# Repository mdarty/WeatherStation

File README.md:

# WeatherStation
ESP32 Weather Station
Weather_Station.jpeg

## WARNING
This is my first C++ program so good luck haha.

## USE
Copy Example_settings.h to settings.h and fill in your info

## Dependincies
All are in the arduino libraries.
  * APRS-IS
  * ArduinoJson
  * driver/adc
  * ESP32Time
  * esp_system
  * LTR390
  * math
  * PubSubClient
  * SparkFunBME280
  * WiFi
  * Wire

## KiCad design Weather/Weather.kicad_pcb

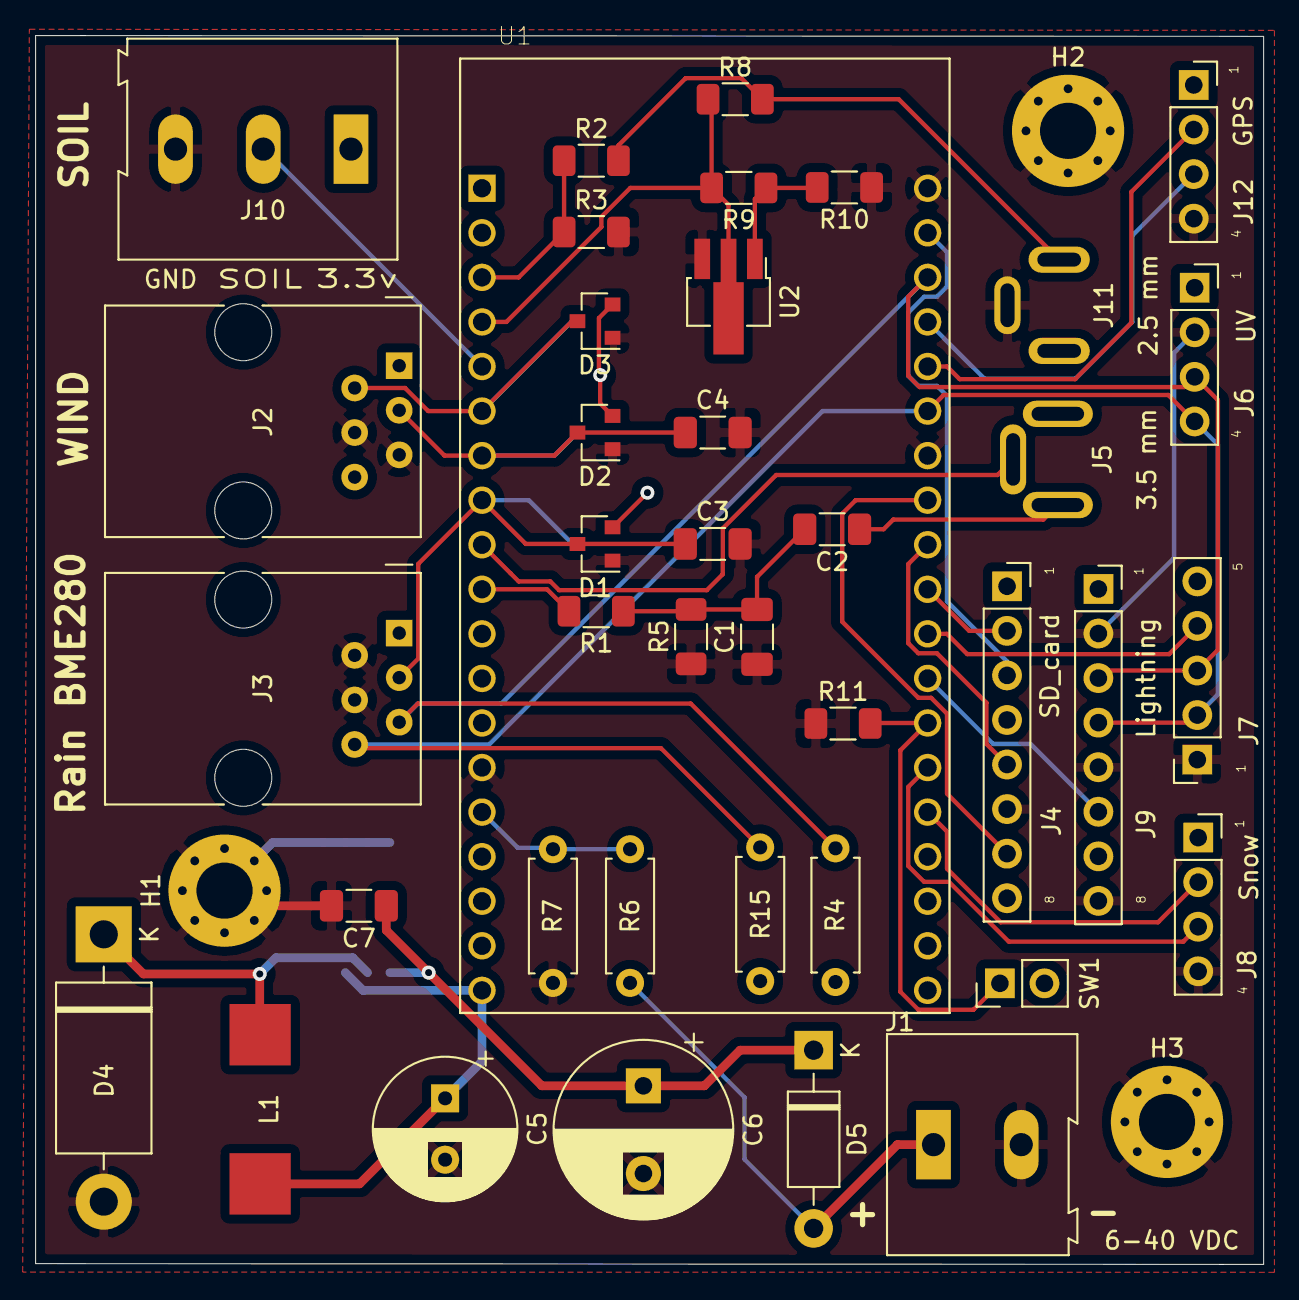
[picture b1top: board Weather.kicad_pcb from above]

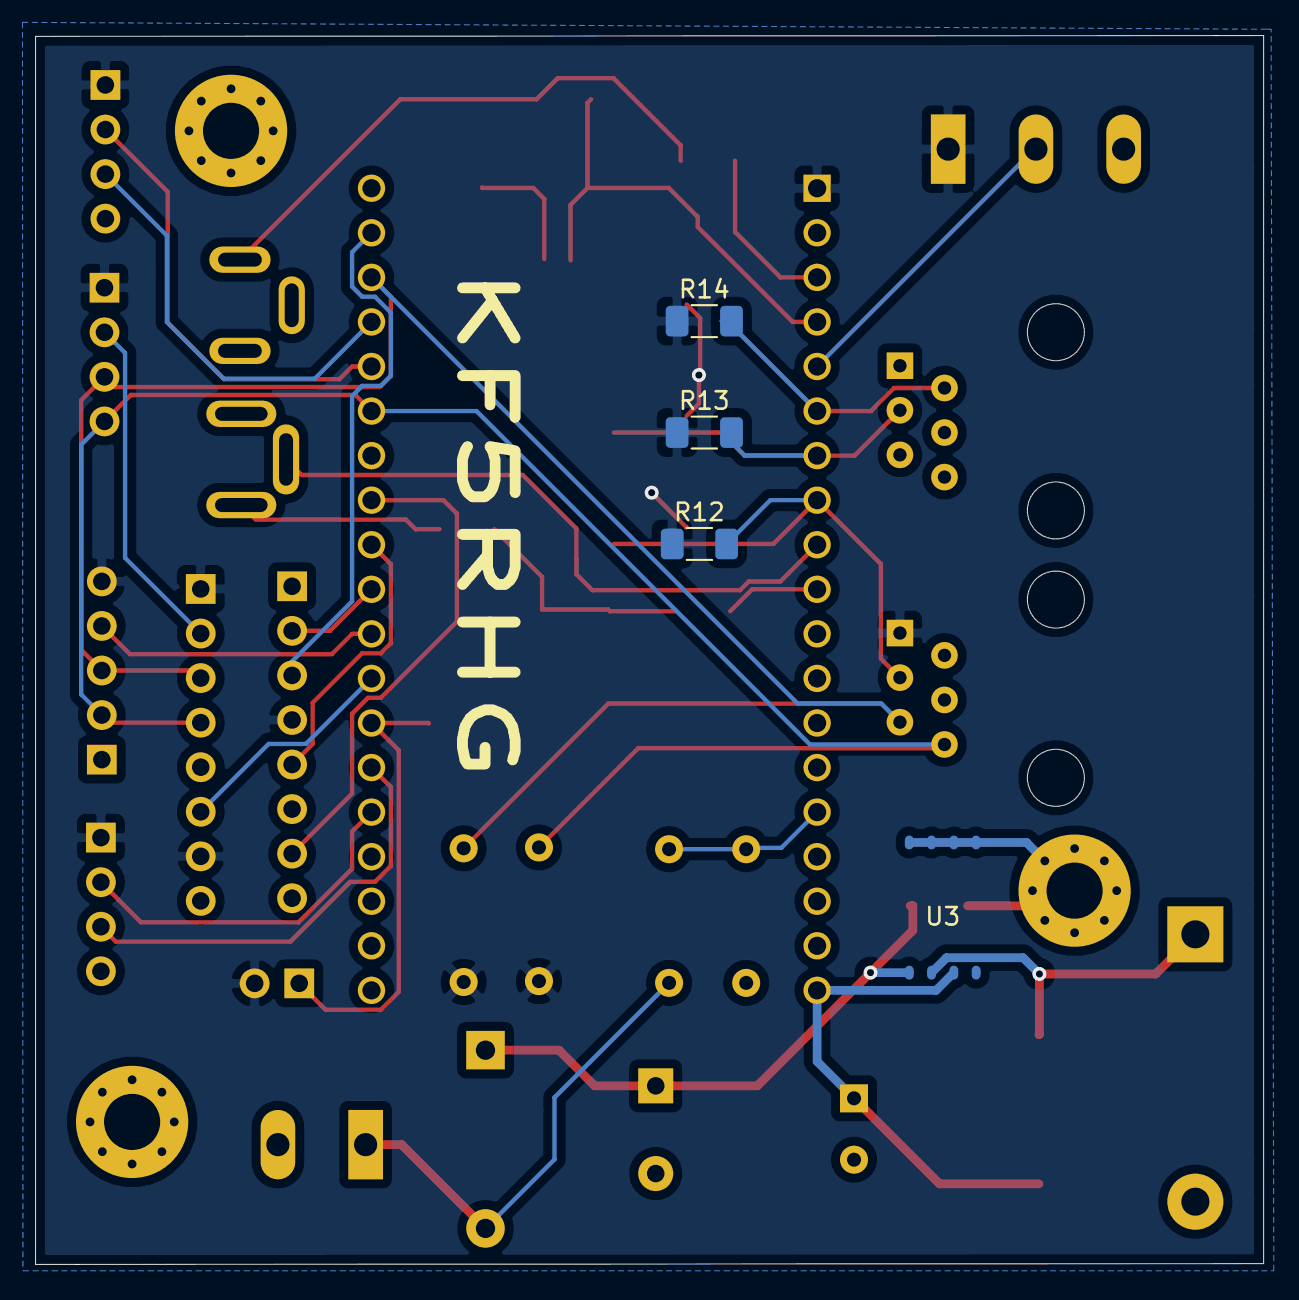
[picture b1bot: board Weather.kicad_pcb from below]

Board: 2 copper layers, 70.0 x 70.0 mm, 47 parts (4 on the bottom side), 32 nets.

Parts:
C1: 4.7nF; C_1206_3216Metric_Pad1.33x1.80mm_HandSolder
C2, C3, C4: 0.1 uF; C_1206_3216Metric_Pad1.33x1.80mm_HandSolder
C5: 180uf/35V; CP_Radial_D8.0mm_P3.50mm
C6: 470uf/35V; CP_Radial_D10.0mm_P5.00mm
C7: 105; C_1206_3216Metric_Pad1.33x1.80mm_HandSolder
D1, D2, D3: BAV99; SOT-23
D4: 1N5820; D_DO-201AD_P15.24mm_Horizontal
D5: 1N5819; D_DO-41_SOD81_P10.16mm_Horizontal
H1, H2: MountingHole_Pad; MountingHole_3.2mm_M3_Pad_Via
H3: MP; MountingHole_3.2mm_M3_Pad_Via
J1: 6-40 VDC; TerminalBlock_Altech_AK300-2_P5.00mm
J2: RJ12 - Wind; RJ12_Amphenol_54601
J3: RJ12 - Rain; RJ12_Amphenol_54601
J4: SD_card; PinSocket_1x08_P2.54mm_Vertical
J5: 3.5 mm; 3.5mm_Stereo_Jack
J6: UV; PinSocket_1x04_P2.54mm_Vertical
J7: RTC; PinSocket_1x05_P2.54mm_Vertical
J8: Snow; PinSocket_1x04_P2.54mm_Vertical
J9: Lightning; PinSocket_1x08_P2.54mm_Vertical
J10: Soil; TerminalBlock_Altech_AK300-3_P5.00mm
J11: 2.5 mm; 2.5mm_Stereo_Jack
J12: GPS; PinSocket_1x04_P2.54mm_Vertical
L1: 68uh/2A; inductor_1004_SMD
R1: 33K; R_1206_3216Metric_Pad1.30x1.75mm_HandSolder
R2, R8: 10K; R_1206_3216Metric_Pad1.30x1.75mm_HandSolder
R3: 3.3K; R_1206_3216Metric_Pad1.30x1.75mm_HandSolder
R4, R6, R7, R15: ??; R_Axial_DIN0207_L6.3mm_D2.5mm_P7.62mm_Horizontal
R5: 1K; R_1206_3216Metric_Pad1.30x1.75mm_HandSolder
R9: 22K; R_1206_3216Metric_Pad1.30x1.75mm_HandSolder
R10: 100K; R_1206_3216Metric_Pad1.30x1.75mm_HandSolder
R11, R14: 10k; R_1206_3216Metric_Pad1.30x1.75mm_HandSolder
R12, R13: 43k; R_1206_3216Metric_Pad1.30x1.75mm_HandSolder
SW1: SW_SPST; PinHeader_1x02_P2.54mm_Vertical
U1: ESP32-DEVKITC-32D; MODULE_ESP32-DEVKITC-32D
U2: CJ431; SOT-89-3_Handsoldering
U3: XL1509-5.0E1; SOIC-8_5x4

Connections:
3.3v: D1.2, D2.2, D3.2, J3.1, J4.4, J6.1, J7.5, J8.1, J9.1, J9.7, J10.1, J12.1, R4.1, R12.1, R13.1, R14.1, R15.1, SW1.2, U1.1
5v: C5.1, L1.1, U1.19, U3.3
ADC: R2.1, R3.1, U1.3
BAT: D5.2, J1.1, R6.1
B_spkr: J11.T, R2.2, R8.2
Chr: R6.2, R7.1, U1.15
DAC: R1.2, U1.10
Echo: J8.3, U1.33
GND: C1.1, C3.2, C4.2, C5.2, C6.2, C7.2, D1.1, D2.1, D3.1, D4.2, H1.1, H2.1, H3.1, J1.2, J2.4, J2.5, J3.2, J3.4, J4.6, J6.2, J7.1, J8.4, J9.2, J9.5, J9.8, J10.3, J11.S, J12.4, R3.2, R5.1, R7.2, R10.1, R11.1, U1.14, U1.20, U1.26, U2.3, U3.5, U3.6, U3.7, U3.8
IRQ: J9.6, U1.31
MFP: J7.4, U1.30
unnamed: C1.2, C2.2, R1.1, R5.2
unnamed: C6.1, C7.1, D5.1, U3.1
unnamed: D4.1, L1.2, U3.2
unnamed: R9.1, R10.2, U2.1
PTT: J5.S, U1.9
RX: J12.2, U1.24
Rain: C3.1, D1.3, J3.3, R12.2, U1.8
SCL: J3.5, J6.3, J7.3, J9.3, R4.2, U1.22
SDA: J3.6, J6.4, J7.2, J9.4, R15.2, U1.25
SD_CS: J4.2, U1.29
SD_safe: R11.2, SW1.1, U1.32
SOIL: J10.2, U1.5
SPI_CIPO: J4.7, U1.27
SPI_COPI: J4.3, U1.21
SPI_SCK: J4.5, U1.28
TX: J12.3, U1.23
Trig: J8.2, U1.34
Wdir: D3.3, J2.2, R14.2, U1.6
Wspd: C4.1, D2.3, J2.3, R13.2, U1.7
b_mic: C2.1, J5.R
trigger: R8.1, R9.2, U1.4, U2.2

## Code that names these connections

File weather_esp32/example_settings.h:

#ifndef SETTINGS_H_
#define SETTINGS_H_

//#define DEBUG
#define APRS
#define MQTT
#define SLEEP

//Debouncing Time in MICROSECONDS (15 Milla seconds)
const int DEBOUNCING_TIME = 15000;

#ifdef DEBUG
  const int report_time = 30000;
#else 
  const int report_time = 300000;
#endif

const int sample_time = 5000;

const char* ntpServer = "SOME NTP SERVER";
const int daylightOffset_sec = 0;
const int gmtOffset_sec = 0;
const unsigned int ntp_time = 3600000;

// Wifi Info
const char* WIFI_NAME = "YOUR WIFI";
const char* WIFI_KEY = "YOUR WIFI PASS";

// Pins
#define I2C_ADDRESS 0x48
const byte RAIN_PIN = 33;
#define WDIR_PIN ADS1115_COMP_0_GND
const byte WSPD_PIN = 32;
//const byte bat_pin = 13;
#define bat_pin ADS1115_COMP_2_GND
#define solar_pin ADS1115_COMP_3_GND
const byte PWM_C = 35;
const byte bat_temp_pin = 27;
const unsigned int solar_full = 2600;
const unsigned int bat_full = 2600; //mV scaled with resistor
const unsigned int bat_emp = 2000; //mV scaled with resistor
#define SOIL_PIN ADS1115_COMP_1_GND
const float Vref = 3291.625;
const unsigned int BULK_CH_SP = 14400;
const unsigned int  FLOAT_CH_SP = 13500;

#ifdef APRS
// Device name and software version
const char *NODENAME = "WxESP";
const char *VERSION = "0.1";
bool       PROBE  = true;                   // True if the station is being probed

const char* APRS_SERVER = "rotate.aprs2.net";
const int   APRS_PORT   = 14580;
const char* APRS_USER   = "YOUR CALLSIGN";
String APRS_SSID   = "-13";
String APRS_HEADER      = ">APRS,TCPIP*:";
const char* APRS_PASS   = "YOUR APRS PIN";
const char* APRS_TOOL   = "ESP32-WX";
const char* APRS_VERS   = "0.1";
String aprsLocation  = "latN/LongW";
#endif

#ifdef MQTT
#include <ArduinoJson.h>
// MQTT
const char* mqtt_server = "MQTT_SERVER";
const int mqtt_port = 1883;
const char* mqtt_clientID = "WeatherStation";
const char* mqtt_user = "MQTT_USER";
const char* mqtt_pass = "MQTT_PASS";
String hassio_topic = "homeassistant/sensor/" + String(mqtt_clientID) + "/";
const int mqtt_buf = 1024;
const char* mqtt_LWT_p = "Online";
String mqtt_LWT = hassio_topic + "LWT";
String mqtt_state_topic = hassio_topic + "state";

String mqtt_configs(byte i) {
  DynamicJsonDocument conf_doc(mqtt_buf);
  JsonObject conf_dev  = conf_doc.createNestedObject("dev");

  conf_dev["name"] = mqtt_clientID;
  conf_dev["mf"] = "Darty";
  conf_dev["sw"] = "0.1";
  conf_dev["ml"] = "Prototype";
  conf_dev["sa"] = "Outside";
  JsonArray ids = conf_dev.createNestedArray("ids");
  ids.add("Prototype");

  switch(i) {
    case 0 :
      conf_doc["unique_id"] = String(mqtt_clientID) + "_temp";
      conf_doc["device_class"] = "temperature";
      conf_doc["name"] = "Outside Temperature";
      conf_doc["unit_of_meas"] = "°F";
      conf_doc["value_template"] = "{{ value_json.Temp }}";
      break;
    case 1 :
      //Humidity
      conf_doc["unique_id"] = String(mqtt_clientID) + "_humidity";
      conf_doc["device_class"] = "humidity";
      conf_doc["name"] = "Outside Humidity";
      conf_doc["unit_of_meas"] = "%";
      conf_doc["value_template"] = "{{ value_json.RH }}";
      break;
    case 2 :
      //Pressure
      conf_doc["unique_id"] = String(mqtt_clientID) + "_pressure";
      conf_doc["device_class"] = "pressure";
      conf_doc["name"] = "Outdoor Temperature";
      conf_doc["unit_of_meas"] = "hPa";
      conf_doc["value_template"] = "{{ value_json.Pres }}";
      break;
    case 3 :
      //Wind Direction
      conf_doc["unique_id"] = String(mqtt_clientID) + "_wind_direction";
      conf_doc["name"] = "Wind Direction";
      conf_doc["icon"] = "mdi:compass";
      conf_doc["unit_of_meas"] = "deg";
      conf_doc["value_template"] = "{{ value_json.wDir }}";
      break;
    case 4 :
      // Wind Speed
      conf_doc["unique_id"] = String(mqtt_clientID) + "_wind_speed";
      conf_doc["name"] = "Wind Speed";
      conf_doc["icon"] = "mdi:weather-windy";
      conf_doc["unit_of_meas"] = "mph";
      conf_doc["value_template"] = "{{ value_json.wSpd }}";
      break;
    case 5 :
      // Wind Gust
      conf_doc["unique_id"] = String(mqtt_clientID) + "_wind_gust";
      conf_doc["name"] = "Wind Gust";
      conf_doc["icon"] = "mdi:weather-windy";
      conf_doc["unit_of_meas"] = "mph";
      conf_doc["value_template"] = "{{ value_json.wGust }}";
    case 6 :
      //Rain Last Hour
      conf_doc["unique_id"] = String(mqtt_clientID) + "_rain_last_hour";
      conf_doc["name"] = "Rain Last Hour";
      conf_doc["icon"] = "mdi:weather-rainy";
      conf_doc["unit_of_meas"] = "in";
      conf_doc["value_template"] = "{{ value_json.rLstHr }}";
      break;
    case 7 :
      //Rain Last 24 hours
      conf_doc["unique_id"] = String(mqtt_clientID) + "_rain_last_24hrs";
      conf_doc["name"] = "Rain Last 24 Hours";
      conf_doc["icon"] = "mdi:weather-rainy"; 
      //conf_doc["state_topic"] = mqtt_topic;
      conf_doc["unit_of_meas"] = "in";
      conf_doc["value_template"] = "{{ value_json.rLst24hrs }}";
      break;
    case 8 :
      //Rain Since Midnight
      conf_doc["unique_id"] = String(mqtt_clientID) + "_rain_since_midnight";
      conf_doc["name"] = "Rain Since Midnight";
      conf_doc["icon"] = "mdi:weather-rainy";
      conf_doc["unit_of_meas"] = "in";
      conf_doc["value_template"] = "{{ value_json.rMidngt }}";
      break;
    case 9 :
    //Soil Moisture
      conf_doc["unique_id"] = String(mqtt_clientID) + "_soil_moisture";
      conf_doc["name"] = "Soil Moisture";
      conf_doc["icon"] = "mdi:water-percent";
      conf_doc["unit_of_meas"] = "%";
      conf_doc["value_template"] = "{{ value_json.SoilMoisture }}";
      break;
    case 10 :
      //Battery
      conf_doc["unique_id"] = String(mqtt_clientID) + "_battery";
      conf_doc["device_class"] = "battery";
      conf_doc["name"] = "WS_Battery";
      conf_doc["unit_of_meas"] = "%";
      conf_doc["value_template"] = "{{ value_json.Battery }}";
      break;
    case 11 :
      //Time
      conf_doc["unique_id"] = String(mqtt_clientID) + "_timestamp";
      conf_doc["device_class"] = "timestamp";
      conf_doc["name"] = "WS Time"; 
      conf_doc["value_template"] = "{{ value_json.Time }}";
      break;
    case 12 :
      conf_doc["unique_id"] = String(mqtt_clientID) + "_bat_mode";
      conf_doc["name"] = "WS Battery Mode";
      conf_doc["value_template"] = "{{ value_json.batMode }}";
      break;
    case 13 :
      conf_doc["unique_id"] = String(mqtt_clientID) + "_bat_duty";
      conf_doc["name"] = "WS Battery Duty";
      conf_doc["value_template"] = "{{ value_json.batDuty }}";
      break;
    case 14 :
      conf_doc["unique_id"] = String(mqtt_clientID) + "_bat_temp";
      conf_doc["name"] = "WS Battery Temp";
      conf_doc["value_template"] = "{{ value_json.batTemp }}";
      break;
    case 15 :
      conf_doc["unique_id"] = String(mqtt_clientID) + "_solarV";
      conf_doc["device_class"] = "Voltage";
      conf_doc["name"] = "WS Solar Voltage";
      conf_doc["unit_of_meas"] = "mV";
      conf_doc["value_template"] = "{{ value_json.solarV }}";
      break;
    case 16 :
      conf_doc["unique_id"] = String(mqtt_clientID) + "_bat_mV";
      conf_doc["device_class"] = "Voltage";
      conf_doc["name"] = "WS Battery Voltage";
      conf_doc["unit_of_meas"] = "mV";
      conf_doc["value_template"] = "{{ value_json.batteryV }}";
      break;
    }

  conf_doc["object_id"] = "sensor." + conf_doc["unique_id"].as<String>();
  conf_doc["avty_t"] = mqtt_LWT;
  conf_doc["pl_avail"] = "Online";
  conf_doc["pl_not_avail"] = "Offline";
  conf_doc["config_topic"] = hassio_topic + conf_doc["unique_id"].as<String>() + "/config";
  conf_doc["state_topic"] = mqtt_state_topic;
  conf_doc["force_update"] = true;
  String out = "";
  serializeJson(conf_doc, out);
  return out;
}

const byte conf_count = 16;
#endif

#endif

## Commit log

2022-05-15 Adding inital Arduino Code and KiCad
2022-05-15 Reorganized stuff and updated Wind Directions
2022-05-16 Updated serial nightmare
2022-05-16 Fixed Serial Nightmare and corrected spelling
2022-05-18 Configured hassio and Updated time and fixed wind and rain bugs
2022-05-26 Added ADS1115, fixed wdir, soil, worked on hassio, but it still doesn't perform discovery properly
2022-05-26 Next try at MQTT discovery
2022-06-03 Reorganized and added WiFi Sleep
2022-06-20 Solar Panel Battery Charger
2022-06-20 Missed some files and corrected a resistor setup
2022-07-17 Fixed rounding and reporting errors
2022-07-17 Fixed APRS time error, And it seems to be working now
